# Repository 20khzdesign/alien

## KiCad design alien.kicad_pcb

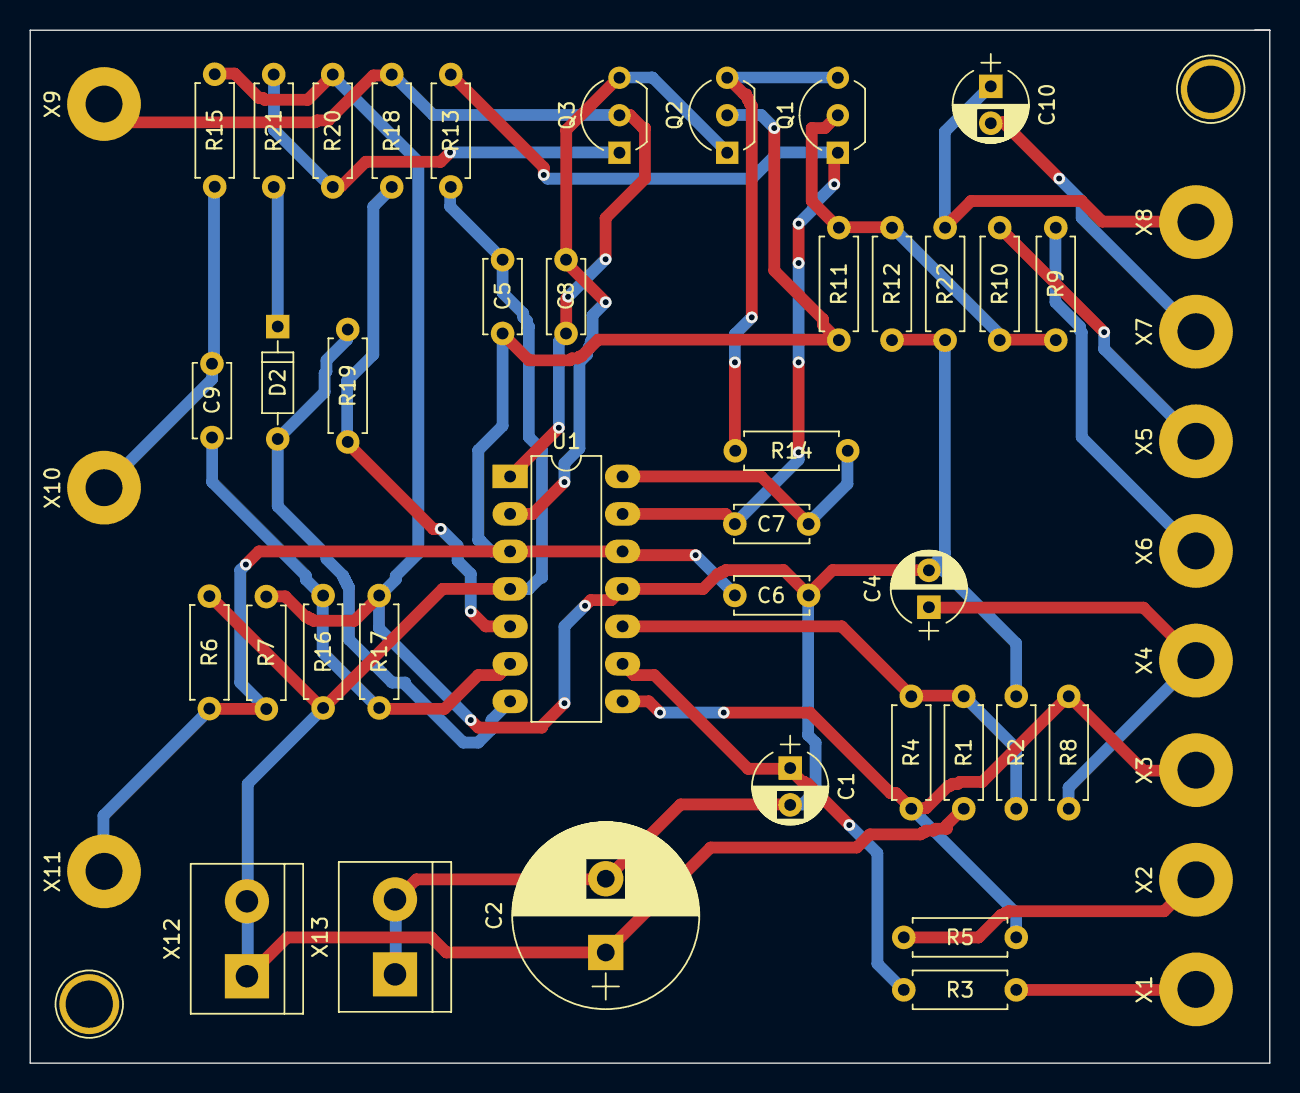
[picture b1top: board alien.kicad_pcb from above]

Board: 2 copper layers, 84.0 x 70.0 mm, 49 parts (0 on the bottom side), 25 nets.

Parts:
C1, C4, C10: 1uF; CP_Radial_D5.0mm_P2.50mm
C2: 470uF; CP_Radial_D12.5mm_P5.00mm
C5, C6: 0.1uF; C_Disc_D5.0mm_W2.5mm_P5.00mm
C7: 100pF; C_Disc_D5.0mm_W2.5mm_P5.00mm
C8: 0.001uF; C_Disc_D5.0mm_W2.5mm_P5.00mm
C9: 0.01; C_Disc_D5.0mm_W2.5mm_P5.00mm
D2: D; D_DO-35_SOD27_P7.62mm_Horizontal
Q1, Q2: 2N390; TO-92_Inline_Wide
Q3: 2N5457; TO-92_Inline_Wide
R1, R2, R4, R9, R15: 100k; R_Axial_DIN0207_L6.3mm_D2.5mm_P7.62mm_Horizontal
R3: 3k; R_Axial_DIN0207_L6.3mm_D2.5mm_P7.62mm_Horizontal
R5, R6, R7: 4k7; R_Axial_DIN0207_L6.3mm_D2.5mm_P7.62mm_Horizontal
R8, R10: 75k; R_Axial_DIN0207_L6.3mm_D2.5mm_P7.62mm_Horizontal
R11: 2k; R_Axial_DIN0207_L6.3mm_D2.5mm_P7.62mm_Horizontal
R12: 220k; R_Axial_DIN0207_L6.3mm_D2.5mm_P7.62mm_Horizontal
R13, R20: 2M; R_Axial_DIN0207_L6.3mm_D2.5mm_P7.62mm_Horizontal
R14, R16, R18, R21: 10k; R_Axial_DIN0207_L6.3mm_D2.5mm_P7.62mm_Horizontal
R17: 15k; R_Axial_DIN0207_L6.3mm_D2.5mm_P7.62mm_Horizontal
R19: 300k; R_Axial_DIN0207_L6.3mm_D2.5mm_P7.62mm_Horizontal
R22: 150k; R_Axial_DIN0207_L6.3mm_D2.5mm_P7.62mm_Horizontal
U1: LM324; DIP-14_W7.62mm_LongPads
X1, X2, X3, X4, X5, X6, X7, X8, X9, X10, X11: JD_CONN_01X01; MountingHole_2.5mm_Pad
X12, X13: JD_CONN_01X02; bornier2

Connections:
+9VA: C2.1, C5.2, R1.1, R6.1, R13.2, R16.2, U1.4, X12.1, X12.2
-9VA: C1.2, C2.2, C4.2, C6.1, R2.2, R7.2, R12.1, R15.2, R17.1, R20.1, R22.1, U1.11, X13.1, X13.2
GNDREF: C5.1, C6.2, Q2.2, R6.2, R7.1, R11.1, U1.3, U1.12, X11.1
unnamed: C1.1, R3.2, U1.9
unnamed: R4.1, R5.1, R8.2, U1.8, X3.1
unnamed: C4.1, R8.1, X4.1
unnamed: C7.1, R14.1, U1.14
unnamed: C7.2, Q1.1, R13.1, U1.13
unnamed: C8.1, Q3.2, R18.1, U1.1, X9.1
unnamed: C8.2, Q2.1, Q3.3, U1.2
unnamed: C9.1, R16.1, R17.2, U1.6
unnamed: C9.2, R15.1, X10.1
unnamed: C10.1, R22.2, X8.1
unnamed: C10.2, X7.1
unnamed: R5.2, X2.1
unnamed: D2.1, R21.2
unnamed: D2.2, R19.2, U1.7
unnamed: Q1.2, R9.1, R10.1, R11.2, R12.2
unnamed: Q1.3, Q2.3, R14.2
unnamed: Q3.1, R20.2, R21.1
unnamed: R1.2, R2.1, R4.2, U1.10
unnamed: R3.1, X1.1
unnamed: R9.2, X6.1
unnamed: R10.2, X5.1
unnamed: R18.2, R19.1, U1.5

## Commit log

2017-06-05 importacion inicial
2017-06-05 solo falta el amplificador de audio
2017-06-05 alimentación
2017-06-06 erc ok
2017-07-20 conectores para panel
2017-07-21 comenzando a asignar huellas
2017-07-22 asignación de huellas
2017-07-22 lista asignación de huellas
2017-07-24 casi para enrutar
2017-07-25 empezamos a enrutar
2017-07-25 primera versión con autorouting
2017-07-25 amo que nos vamos
2017-09-06 corrección de la posición de las patas de los transistores
